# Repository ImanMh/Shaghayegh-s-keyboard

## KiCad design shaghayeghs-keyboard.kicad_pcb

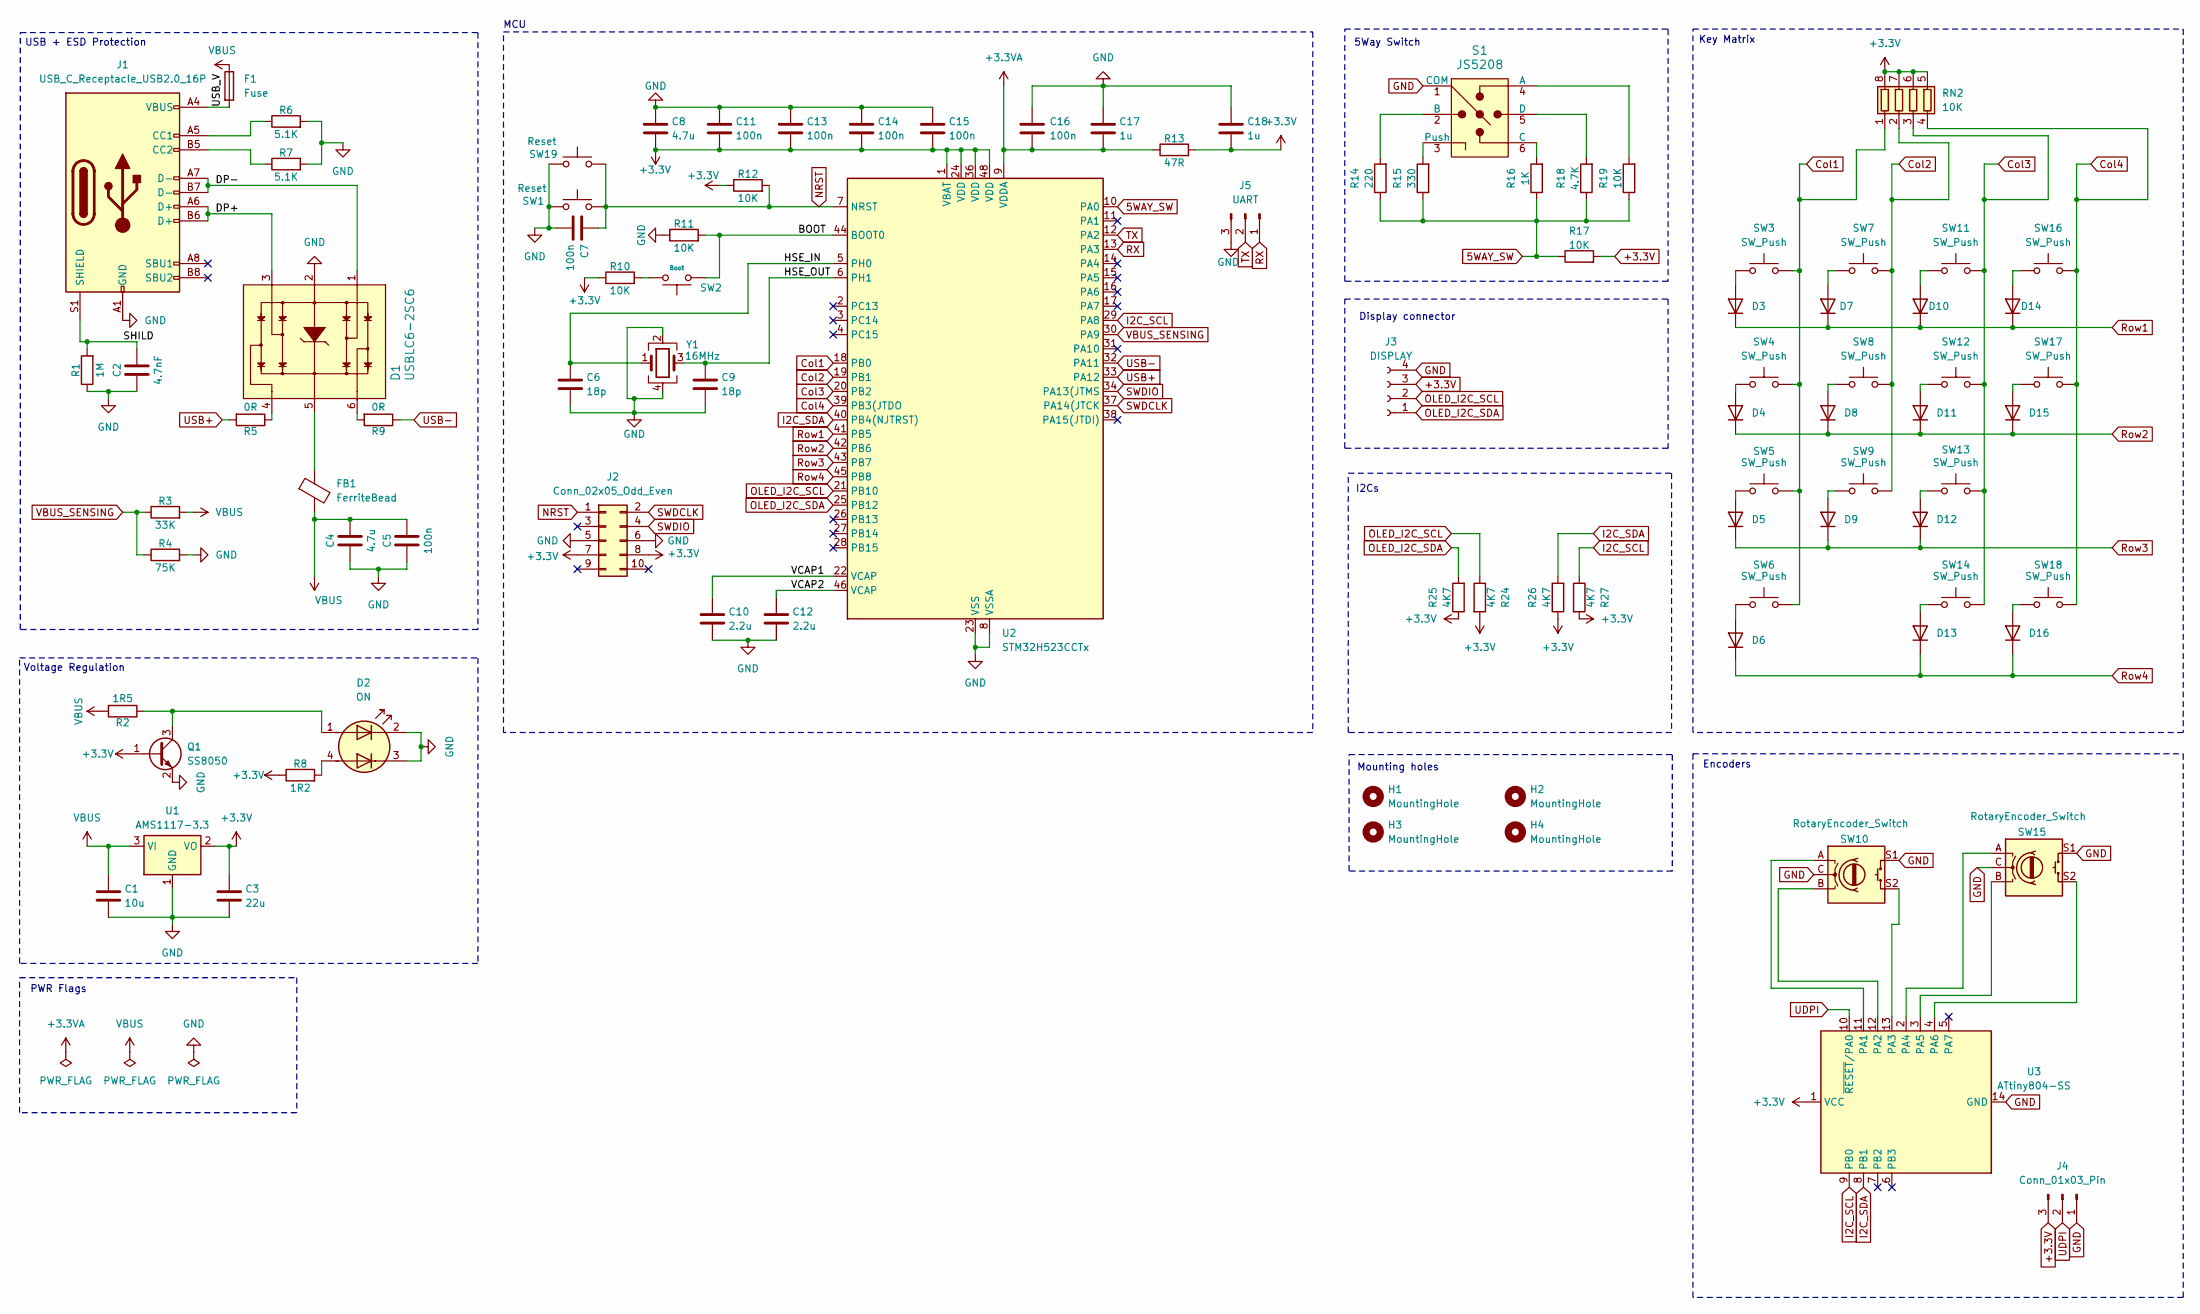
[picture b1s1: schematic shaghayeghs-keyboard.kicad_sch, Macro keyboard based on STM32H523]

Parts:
C1: 10u; C_1206_3216Metric
C2: 4.7nF; C_0603_1608Metric
C3: 22u; C_1206_3216Metric
C4, C8: 4.7u; C_0805_2012Metric
C5, C7, C11, C13, C14, C15, C16: 100n; C_0603_1608Metric
C6, C9: 18p; C_0603_1608Metric
C10, C12: 2.2u; C_0805_2012Metric
C17, C18: 1u; C_0603_1608Metric
D1: USBLC6-2SC6; SOT23-6L; MPN USBLC6-2SC6; Digi-Key_PN 497-5235-1-ND
D2: ON; LED_Kingbright_APHBM2012_2x1.25mm
D3, D4, D5, D6, D7, D8, D9, D10, D11, D12, D13, D14, D15, D16: 1N4148WT; D_SOD-123
F1: Fuse; R_1206_3216Metric
FB1: FerriteBead; R_0603_1608Metric
H1, H2, H3, H4: MountingHole; MountingHole_2.2mm_M2
J1: USB_C_Receptacle_USB2.0_16P; USB_C_Receptacle_GCT_USB4105-xx-A_16P_TopMnt_Horizontal
J2: Conn_02x05_Odd_Even; PinSocket_2x05_P2.54mm_Vertical
J3: DISPLAY; JST_XH_B4B-XH-AM_1x04_P2.50mm_Vertical
J4: Conn_01x03_Pin; PinSocket_1x03_P2.54mm_Vertical
J5: UART; PinSocket_1x03_P2.54mm_Vertical
Q1: SS8050; SOT-23
R1: 1M; R_0603_1608Metric
R2: 1R5; R_0603_1608Metric
R3: 33K; R_0603_1608Metric
R4: 75K; R_0603_1608Metric
R5, R9: 0R; R_0603_1608Metric
R6, R7: 5.1K; R_0603_1608Metric
R8: 1R2; R_0603_1608Metric
R10, R11, R12, R19: 10K; R_0603_1608Metric
R13: 47R; R_0603_1608Metric
R14: 220; R_0603_1608Metric
R15: 330; R_0603_1608Metric
R16: 1K; R_0603_1608Metric
R17: 10K; R_1206_3216Metric
R18: 4.7K; R_0603_1608Metric
R24, R25, R26, R27: 4K7; R_0805_2012Metric
RN2: 10K; R_Array_Convex_4x0402
S1: JS5208; 5Way_switch; MPN JS5208; Digi-Key_PN EG4561-ND
SW1: Reset; SW_SPST_B3U-1000P
SW2: Boot; SW_SPST_B3U-1000P
SW3, SW4, SW5, SW7, SW8, SW9, SW11, SW12, SW13, SW14, SW16, SW18: SW_Push; SW_Cherry_MX_1.00u_PCB_with_3D
SW6, SW17: SW_Push; SW_Cherry_MX_2.00u_PCB
SW10, SW15: RotaryEncoder_Switch; RotaryEncoder_Alps_EC11E-Switch_Vertical_H20mm
SW19: Reset; Tactile Tact Key right angled - Aliexpress
U1: AMS1117-3.3; SOT-223-3_TabPin2
U2: STM32H523CCTx; LQFP-48_7x7mm_P0.5mm
U3: ATtiny804-SS; SOIC-14_3.9x8.7mm_P1.27mm
Y1: 16MHz; Crystal_SMD_3225-4Pin_3.2x2.5mm

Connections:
5WAY_SW: R14.1, R15.1, R16.1, R17.1, R18.1, R19.1, U2.10 (PA0)
+3.3V: C3.1, C8.2, C11.2, C13.2, C14.2, C15.2, C18.2, J2.7, J2.8, J3.3, J4.3, Q1.1 (B), R8.1, R10.1, R12.1, R13.2, R17.2, R24.2, R25.1, R26.1, R27.2, RN2.5 (R4.2), RN2.6 (R3.2), RN2.7 (R2.2), RN2.8 (R1.2), U1.2 (VO), U2.1 (VBAT), U2.24 (VDD), U2.36 (VDD), U2.48 (VDD), U3.1 (VCC)
+3.3VA: C16.2, C17.2, R13.1, U2.9 (VDDA)
/BOOT: R11.2, SW2.1, U2.44 (BOOT0)
/DP+: D1.3, J1.A6 (D+), J1.B6 (D+)
/DP-: D1.1, J1.A7 (D-), J1.B7 (D-)
/HSE_IN: C6.1, U2.5 (PH0), Y1.1
/HSE_OUT: C9.1, U2.6 (PH1), Y1.3
/SHILD: C2.2, J1.S1 (SHIELD), R1.2
/USB_V: F1.2, J1.A4 (VBUS), J1.A9 (VBUS), J1.B4 (VBUS), J1.B9 (VBUS)
/VCAP1: C10.1, U2.22 (VCAP)
/VCAP2: C12.1, U2.46 (VCAP)
Col1: RN2.1 (R1.1), SW3.2, SW4.2, SW5.2, SW6.2, U2.18 (PB0)
Col2: RN2.2 (R2.1), SW7.2, SW8.2, SW9.2, U2.19 (PB1)
Col3: RN2.3 (R3.1), SW11.2, SW12.2, SW13.2, SW14.2, U2.20 (PB2)
Col4: RN2.4 (R4.1), SW16.2, SW17.2, SW18.2, U2.39 (PB3(JTDO)
GND: C1.2, C2.1, C3.2, C4.1, C5.1, C6.2, C7.2, C8.1, C9.2, C10.2, C11.1, C12.2, C13.1, C14.1, C15.1, C16.1, C17.1, C18.1, D1.2, D2.2 (K1), D2.3 (K2), J1.A1 (GND), J1.A12 (GND), J1.B1 (GND), J1.B12 (GND), J2.5, J2.6, J3.4, J4.1, J5.3, Q1.2 (E), R1.1, R4.2, R6.2, R7.2, R11.1, S1.1 (COM), SW1.1, SW10.C, SW10.S1, SW15.C, SW15.S1, SW19.1, U1.1 (GND), U2.8 (VSSA), U2.23 (VSS), U2.35 (VSS), U2.47 (VSS), U3.14 (GND), Y1.2, Y1.4
I2C_SCL: R27.1, U2.29 (PA8), U3.9 (PB0)
I2C_SDA: R26.2, U2.40 (PB4(NJTRST)), U3.8 (PB1)
NRST: C7.1, J2.1, R12.2, SW1.2, SW19.2, U2.7 (NRST)
unnamed: D1.4, R5.1
unnamed: D1.5, FB1.1
unnamed: D1.6, R9.2
unnamed: D2.1 (A1), Q1.3 (C), R2.1
unnamed: D2.4 (A2), R8.2
unnamed: D3.2 (A), SW3.1
unnamed: D4.2 (A), SW4.1
unnamed: D5.2 (A), SW5.1
unnamed: D6.2 (A), SW6.1
unnamed: D7.2 (A), SW7.1
unnamed: D8.2 (A), SW8.1
unnamed: D9.2 (A), SW9.1
unnamed: D10.2 (A), SW11.1
unnamed: D11.2 (A), SW12.1
unnamed: D12.2 (A), SW13.1
unnamed: D13.2 (A), SW14.1
unnamed: D14.2 (A), SW16.1
unnamed: D15.2 (A), SW17.1
unnamed: D16.2 (A), SW18.1
unnamed: J1.A5 (CC1), R6.1
unnamed: J1.B5 (CC2), R7.1
unnamed: R10.2, SW2.2
unnamed: R19.2, S1.4 (A)
unnamed: R14.2, S1.2 (B)
unnamed: R16.2, S1.6 (C)
unnamed: R18.2, S1.5 (D)
unnamed: R15.2, S1.3 (Push)
unnamed: SW10.A, U3.11 (PA1)
unnamed: SW10.B, U3.12 (PA2)
unnamed: SW10.S2, U3.13 (PA3)
unnamed: SW15.A, U3.2 (PA4)
unnamed: SW15.B, U3.3 (PA5)
unnamed: SW15.S2, U3.4 (PA6)
OLED_I2C_SCL: J3.2, R24.1, U2.21 (PB10)
OLED_I2C_SDA: J3.1, R25.2, U2.25 (PB12)
RX: J5.1, U2.13 (PA3)
Row1: D3.1 (K), D7.1 (K), D10.1 (K), D14.1 (K), U2.41 (PB5)
Row2: D4.1 (K), D8.1 (K), D11.1 (K), D15.1 (K), U2.42 (PB6)
Row3: D5.1 (K), D9.1 (K), D12.1 (K), U2.43 (PB7)
Row4: D6.1 (K), D13.1 (K), D16.1 (K), U2.45 (PB8)
SWDCLK: J2.2, U2.37 (PA14(JTCK)
SWDIO: J2.4, U2.34 (PA13(JTMS)
TX: J5.2, U2.12 (PA2)
UDPI: J4.2, U3.10 (~RESET/PA0)
USB+: R5.2, U2.33 (PA12)
USB-: R9.1, U2.32 (PA11)
VBUS: C1.1, C4.2, C5.2, F1.1, FB1.2, R2.2, R3.2, U1.3 (VI)
VBUS_SENSING: R3.1, R4.1, U2.30 (PA9)

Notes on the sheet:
USB + ESD Protection
Voltage Regulation
Encoders
PWR Flags
Key Matrix
Mounting holes
I2Cs
Display connector
MCU
5Way Switch

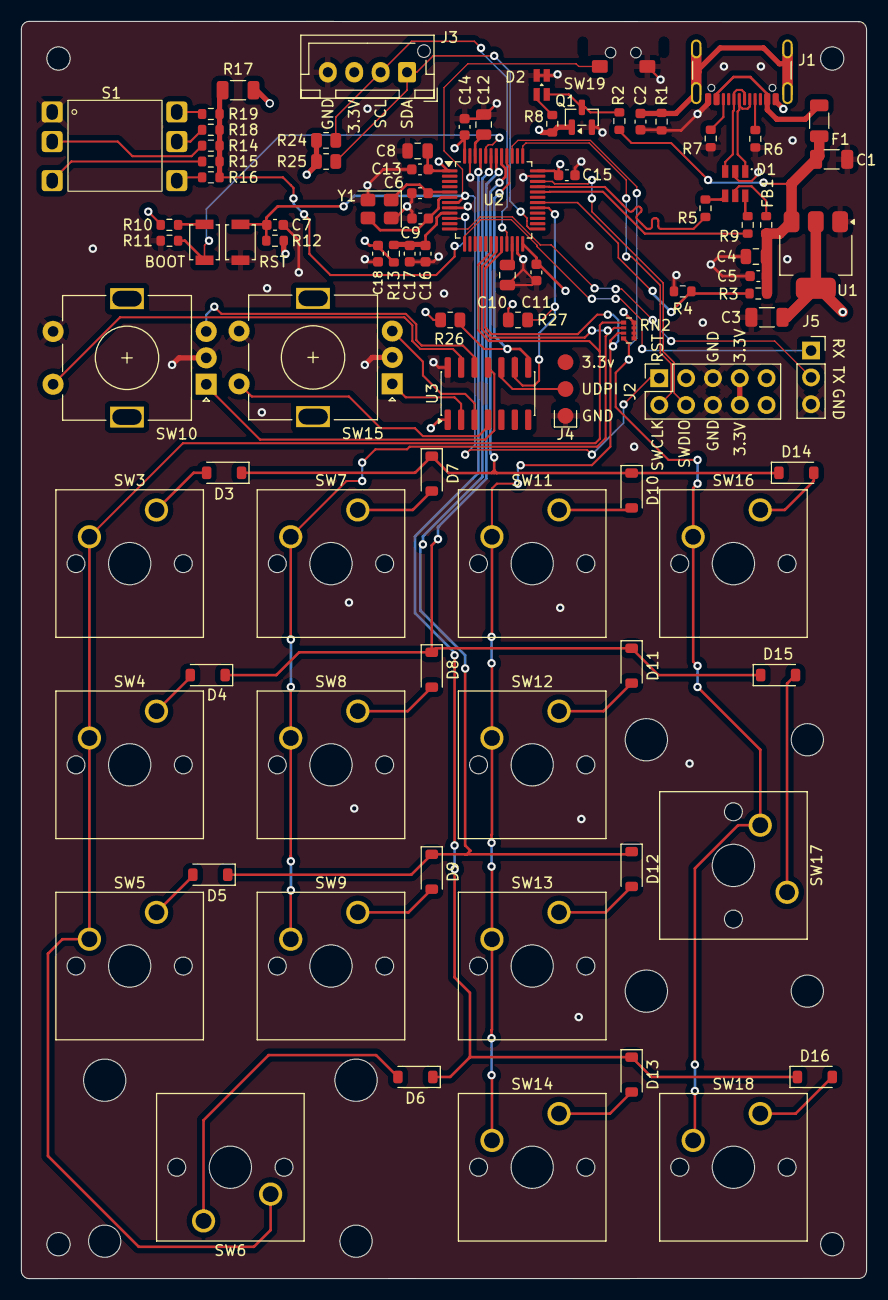
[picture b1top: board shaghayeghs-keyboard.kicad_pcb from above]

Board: 4 copper layers, 80.0 x 119.0 mm, 95 parts (1 on the bottom side), 68 nets.

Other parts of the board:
Macro keyboard based on STM32H523: LOGO; black-dina-4x4

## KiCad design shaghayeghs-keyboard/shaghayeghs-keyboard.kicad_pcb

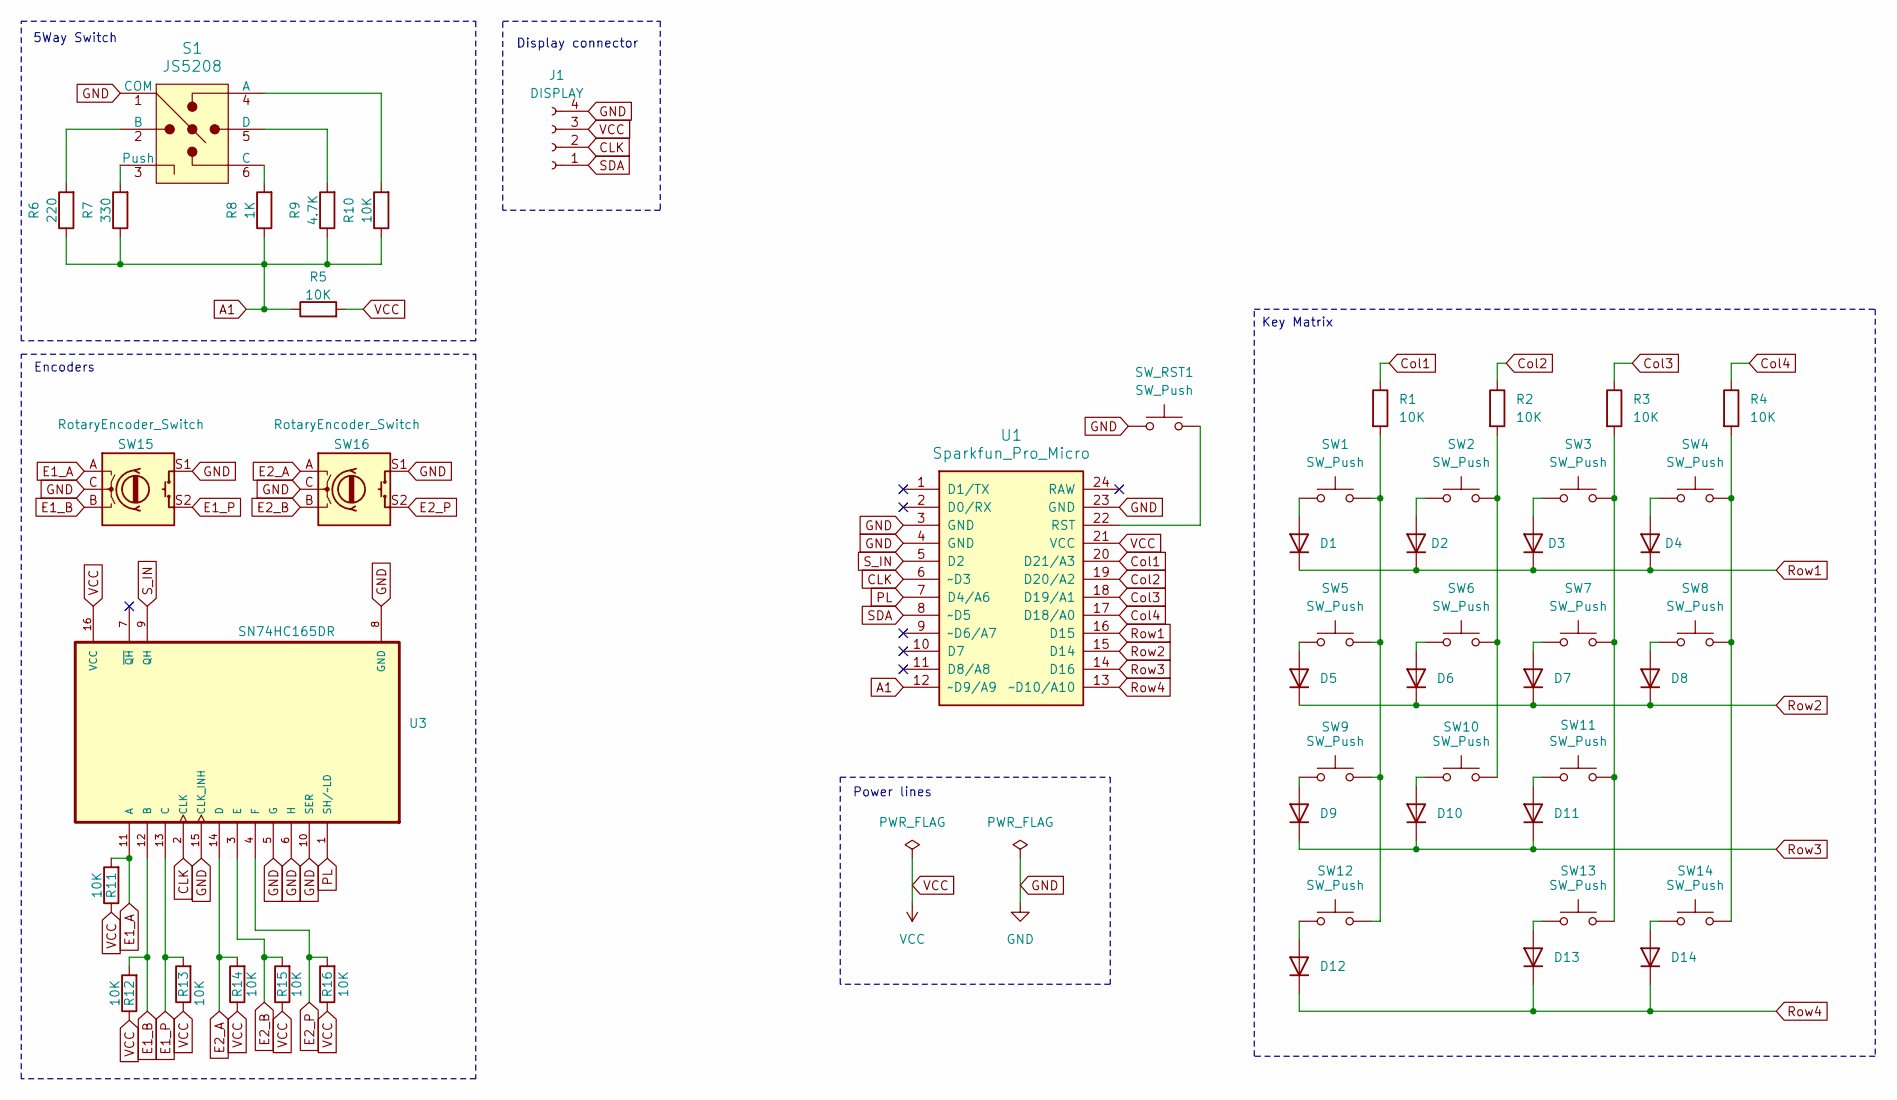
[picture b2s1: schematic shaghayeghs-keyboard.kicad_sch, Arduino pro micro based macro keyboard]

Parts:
D1, D2, D3, D4, D5, D6, D7, D8, D9, D10, D11, D12, D13, D14: 1N4148WT; D_1206_3216Metric
J1: DISPLAY; JST_XH_B4B-XH-AM_1x04_P2.50mm_Vertical
R1, R2, R3, R4, R5, R10, R11, R12, R13, R14, R15, R16: 10K; R_1206_3216Metric
R6: 220; R_1206_3216Metric
R7: 330; R_1206_3216Metric
R8: 1K; R_1206_3216Metric
R9: 4.7K; R_1206_3216Metric
S1: JS5208; 5Way_switch; MPN JS5208; Digi-Key_PN EG4561-ND
SW1, SW2, SW3, SW4, SW5, SW6, SW7, SW9, SW10, SW11, SW13, SW14: SW_Push; SW_Cherry_MX_1.00u_PCB_with_3D
SW8, SW12: SW_Push; SW_Cherry_MX_2.00u_PCB
SW15, SW16: RotaryEncoder_Switch; RotaryEncoder_Alps_EC11E-Switch_Vertical_H20mm
SW_RST1: SW_Push; SW_PUSH_6mm_H4.3mm
U1: Sparkfun_Pro_Micro
U3: SN74HC165DR; SOIC127P600X175-16N

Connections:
A1: R5.1, R6.1, R7.1, R8.1, R9.1, R10.1, U1.12 (~D9/A9)
CLK: J1.2, U1.6 (~D3), U3.2 (CLK)
Col1: R1.1, U1.20 (D21/A3)
Col2: R2.1, U1.19 (D20/A2)
Col3: R3.1, U1.18 (D19/A1)
Col4: R4.1, U1.17 (D18/A0)
E1_A: R11.2, SW15.A, U3.11 (A)
E1_B: R12.2, SW15.B, U3.12 (B)
E1_P: R13.2, SW15.S2, U3.13 (C)
E2_A: R14.2, SW16.A, U3.14 (D)
E2_B: R15.2, SW16.B, U3.3 (E)
E2_P: R16.2, SW16.S2, U3.4 (F)
GND: J1.4, S1.1 (COM), SW15.C, SW15.S1, SW16.C, SW16.S1, SW_RST1.1, U1.3 (GND), U1.4 (GND), U1.23 (GND), U3.5 (G), U3.6 (H), U3.8 (GND), U3.10 (SER), U3.15 (CLK_INH)
unnamed: D1.2 (A), SW1.1
unnamed: D2.2 (A), SW2.1
unnamed: D3.2 (A), SW3.1
unnamed: D4.2 (A), SW4.1
unnamed: D5.2 (A), SW5.1
unnamed: D6.2 (A), SW6.1
unnamed: D7.2 (A), SW7.1
unnamed: D8.2 (A), SW8.1
unnamed: D9.2 (A), SW9.1
unnamed: D10.2 (A), SW10.1
unnamed: D11.2 (A), SW11.1
unnamed: D12.2 (A), SW12.1
unnamed: D13.2 (A), SW13.1
unnamed: D14.2 (A), SW14.1
unnamed: R1.2, SW1.2, SW5.2, SW9.2, SW12.2
unnamed: R2.2, SW2.2, SW6.2, SW10.2
unnamed: R3.2, SW3.2, SW7.2, SW11.2, SW13.2
unnamed: R4.2, SW4.2, SW8.2, SW14.2
unnamed: R10.2, S1.4 (A)
unnamed: R6.2, S1.2 (B)
unnamed: R8.2, S1.6 (C)
unnamed: R9.2, S1.5 (D)
unnamed: R7.2, S1.3 (Push)
unnamed: SW_RST1.2, U1.22 (RST)
PL: U1.7 (D4/A6), U3.1 (SH/~LD)
Row1: D1.1 (K), D2.1 (K), D3.1 (K), D4.1 (K), U1.16 (D15)
Row2: D5.1 (K), D6.1 (K), D7.1 (K), D8.1 (K), U1.15 (D14)
Row3: D9.1 (K), D10.1 (K), D11.1 (K), U1.14 (D16)
Row4: D12.1 (K), D13.1 (K), D14.1 (K), U1.13 (~D10/A10)
SDA: J1.1, U1.8 (~D5)
S_IN: U1.5 (D2), U3.9 (QH)
VCC: J1.3, R5.2, R11.1, R12.1, R13.1, R14.1, R15.1, R16.1, U1.21 (VCC), U3.16 (VCC)

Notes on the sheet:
Encoders
Power lines
Key Matrix
Display connector
5Way Switch

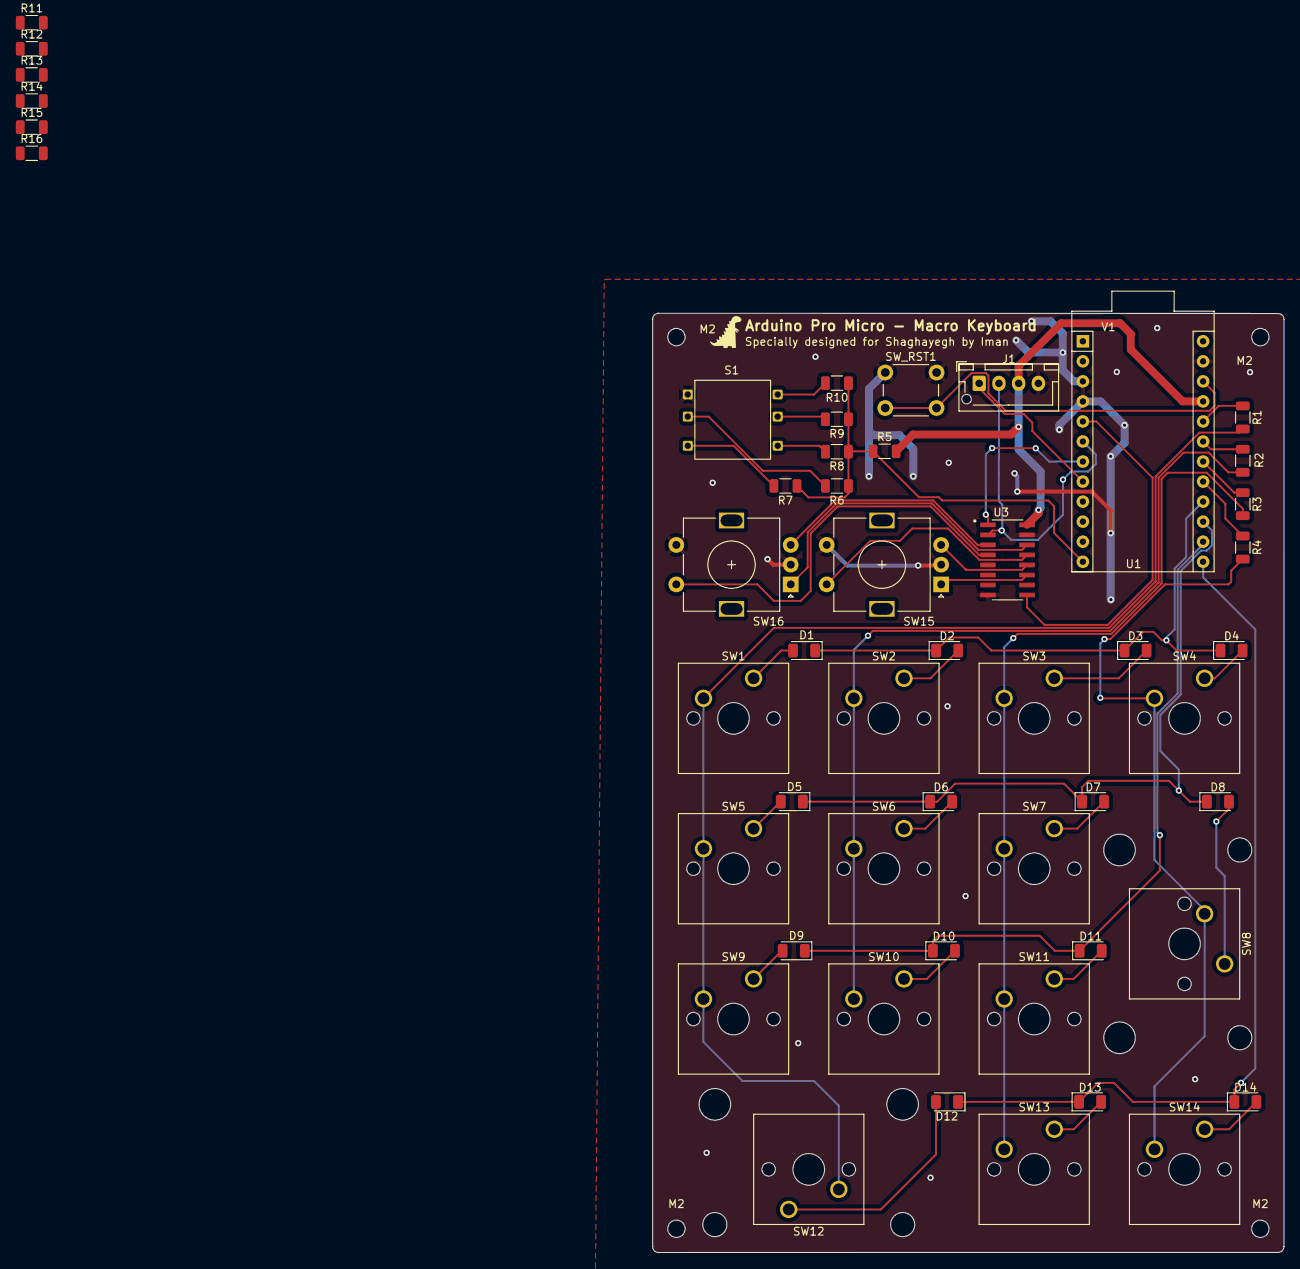
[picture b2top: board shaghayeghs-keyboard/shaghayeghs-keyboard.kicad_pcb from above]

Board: 2 copper layers, 80.0 x 119.0 mm, 56 parts (0 on the bottom side), 45 nets.

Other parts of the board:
Arduino Pro Micro - Macro Keyboard: LOGO; black-dina-4x4
M2, M2#2, M2#3, M2#4: MountingHole_2.2mm_M2

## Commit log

2025-10-05 fixes bad diod footprints
2026-02-14 initial produced version based on Arduino
2026-03-04 First STM32 design
